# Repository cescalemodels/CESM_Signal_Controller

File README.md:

## CESM Signal Decoder Code - DEVELOPMENT BRANCH

Signal controller software for CESM searchlight signals. This code will, once it's done being developed, control CESM signal boards in different configurations, depending on the software used. Pleas see www.cescalemodels.com to learn more about our signalling products.

(C)2017 by David Cutting. Special thanks to Alex Shepard for his support in the development of the code.

This code is licensed under an Attribution-NonCommercial 4.0 International (CC BY-NC 4.0) license. Please see the license (included in the repository) and https://creativecommons.org/licenses/by-nc/4.0/ to learn more about what this means.

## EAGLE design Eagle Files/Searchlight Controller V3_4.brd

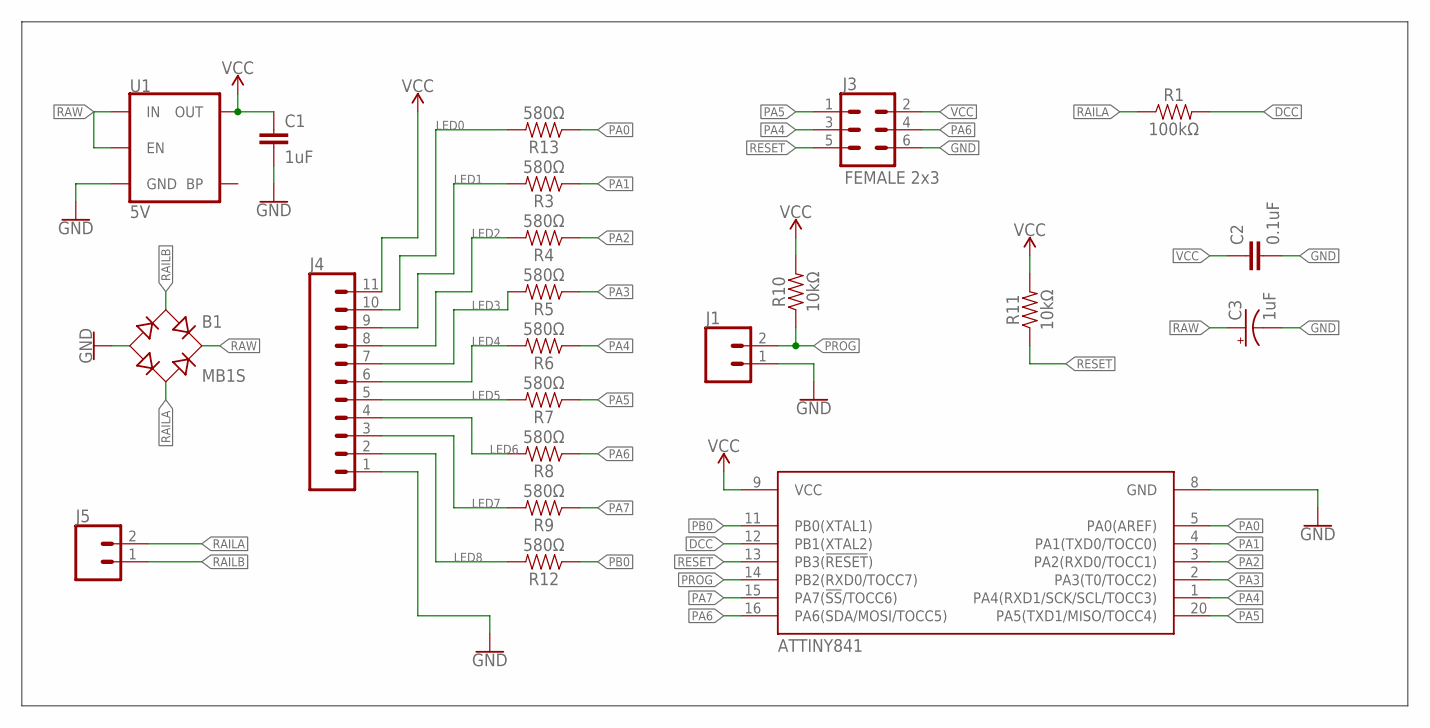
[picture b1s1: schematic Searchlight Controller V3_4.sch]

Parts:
B1: MB1S; SOIC-4
C1: 1uF; 0603
C2: 0.1uF; 0603
C3: 1uF; EIA3216
J1: CONN_02LOCK; 1X02_LOCK
J3: FEMALE 2x3; 2X3
J4: CONN_11LONGPADS; 1X11_LONGPADS
J5: CONN_02; 1X02
R1: 100kΩ; 0603
R3, R4, R5, R6, R7, R8, R9, R12, R13: 580Ω; 0603
R10, R11: 10kΩ; 0603
U1: 5V; SOT23-5
U$1: ATTINY841-MMH; QFN-20-4X4MM

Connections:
DCC: R1.2, U$1.12 (PB1(XTAL2))
GND: B1.-, C1.2, C2.2, C3.-, J1.1, J3.6, J4.1, U1.2 (GND), U$1.8 (GND)
LED0: J4.10, R13.2
LED1: J4.9, R3.2
LED2: J4.8, R4.2
LED3: J4.7, R5.2
LED4: J4.6, R6.2
LED5: J4.5, R7.2
LED6: J4.4, R8.2
LED7: J4.3, R9.2
LED8: J4.2, R12.2
PA0: R13.1, U$1.5 (PA0(AREF))
PA1: R3.1, U$1.4 (PA1(TXD0/TOCC0))
PA2: R4.1, U$1.3 (PA2(RXD0/TOCC1))
PA3: R5.1, U$1.2 (PA3(T0/TOCC2))
PA4: J3.3, R6.1, U$1.1 (PA4(RXD1/SCK/SCL/TOCC3))
PA5: J3.1, R7.1, U$1.20 (PA5(TXD1/MISO/TOCC4))
PA6: J3.4, R8.1, U$1.16 (PA6(SDA/MOSI/TOCC5))
PA7: R9.1, U$1.15 (PA7(!SS!/TOCC6))
PB0: R12.1, U$1.11 (PB0(XTAL1))
PROG: J1.2, R10.1, U$1.14 (PB2(RXD0/TOCC7))
RAILA: B1.~2 (AC2), J5.2, R1.1
RAILB: B1.~1 (AC1), J5.1
RAW: B1.+, C3.+, U1.1 (IN), U1.3 (EN)
RESET: J3.5, R11.1, U$1.13 (PB3(!RESET!))
VCC: C1.1, C2.1, J3.2, J4.11, R10.2, R11.2, U1.5 (OUT), U$1.9 (VCC)

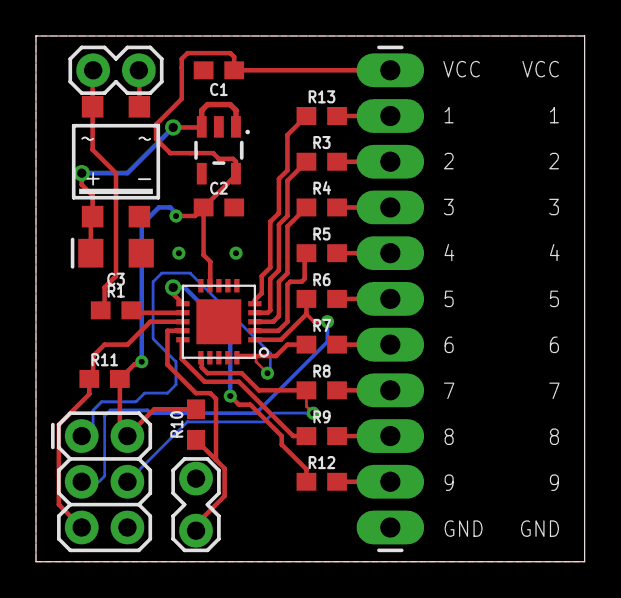
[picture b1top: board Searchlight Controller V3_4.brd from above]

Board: 2 copper layers, 30.5 x 29.2 mm, 22 parts (0 on the bottom side), 26 nets.

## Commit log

2017-04-15 :lollipop: Added .gitattributes & .gitignore files
2017-04-15 Added all code to repository
2017-04-16 Moved code towards funtionality, but it still doen't work because of unknown bug.
2017-04-16 Cleaned up repository and added eagle files
2017-04-16 Added PDF Schematic
2017-05-22 Added latest changes, code is at least stable but lacking special effects and programming in OPS
2017-05-24 Updated code and removed old schematics
2017-05-24 Restructured and updated development branch
2017-05-24 Renamed files to reflect upcoming code variations
2017-05-24 Added "dark" element, code from Alex Shepard added for programming but not yet tested (last commit)
    Still need to tune RGB values
2017-05-25 Attempted to work around Digitrax 9999 issue, but decoder wtill won't program with 8888.
2017-05-28 Added Locomotive OPS Mode Programming support
2017-05-29 Commented code
2017-05-29 Changed color setting logic, comments, added common anode/cathode functionality
    Color setting logic *should* work but still needs to be tested.
2017-06-03 Minor bug fixes
2017-06-03 Reverted to old version
2017-06-03 Reorganized color lookup structure and general layout of code to make it more simple.
2017-06-04 Added beta fading code
2017-06-04 Made the DCC Decoder Address Setting Function a one-shot action until the jumper it removed
2017-06-04 More work on the effects code
2017-06-05 Continued work on the format code and a new approach to the special effects... far from done.
2017-06-05 Added new BoardDefine file to take care of different hardware configurations, as well as some reference code for special effects.
2017-06-06 Finished basic logic for effects. Still need to fix back-end and add flashing.
2017-06-07 Added all special effects and cleaned up code. Compiles but might not work...
2017-06-09 Bug fixes and improvements
2017-06-09 More bug fixes... investigating possible clash between software PWM and nmraDCC library.
2017-06-13 Modified main file
2017-06-20 change struct definitions to typedef struct and make struct and variable names to have different case so they're NOT the same
2017-06-20 Removed non-required code.
2017-06-25 Changed DEFAULT_ADDRESS to now be "+ 1" for CV storage to match up with NmraDcc library change
2017-06-26 Fixed logic and increased PWM speeds. Flashing and vane movement now works. Last step is to get the LED's to turn off at 0 brightness, which they are not doing at the moment.
2017-06-27 Added Serial.print debug to setSoftPWMValues() function to look at the actual PWM values and there are some greater than PWM Max (31)
2017-06-28 Finished all special effects code. Default brightnesses need tweaking, but code is stable.
2017-06-28 Fixed commit issue that was created when merging two pieces of code. Code is now stable and functional... for real.

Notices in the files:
Eagle Files/Searchlight Controller V3_4.brd:
Copyright 2017 CESM
parts and their libraries:
SparkFun-Capacitors: Licensing: Creative Commons ShareAlike 4.0 International - https://creativecommons.org/licenses/by-sa/4.0
